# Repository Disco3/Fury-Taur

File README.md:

# Fury-Taur
Fury-Taur is a dualstage J201 Fuzz that mounts internally on a Push-Pull Pot

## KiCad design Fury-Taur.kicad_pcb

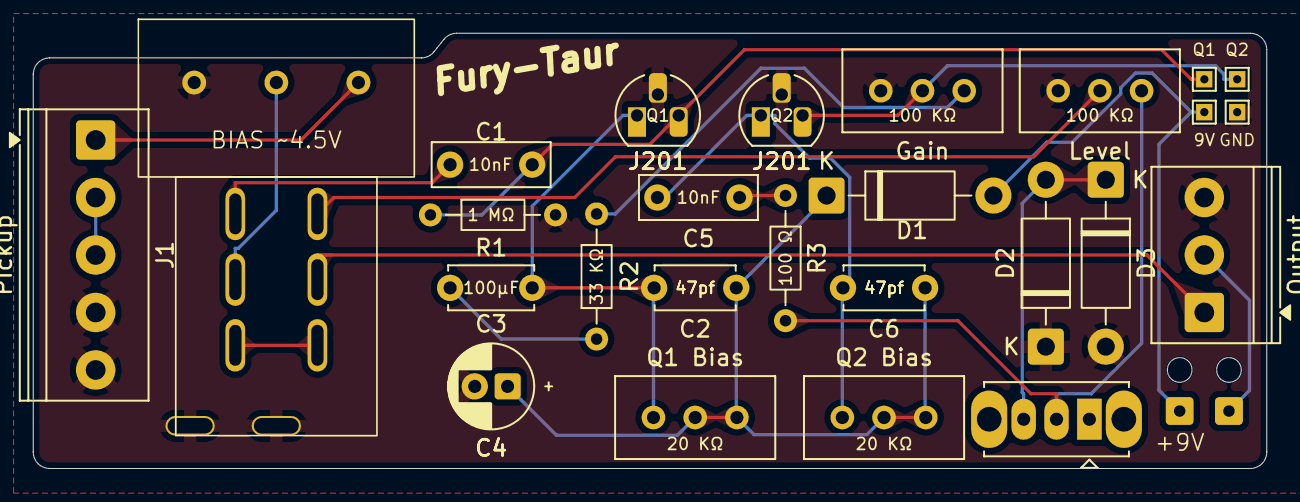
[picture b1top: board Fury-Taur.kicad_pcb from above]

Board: 2 copper layers, 75.1 x 26.5 mm, 30 parts (0 on the bottom side), 20 nets.

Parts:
9V: TestPoint_THTPad_1.0x1.0mm_Drill0.5mm
9V+: SolderWire-0.127sqmm_1x01_D0.48mm_OD1mm
BAT-: SolderWire-0.127sqmm_1x01_D0.48mm_OD1mm
C1, C5: 10nf; C_Disc_D7.0mm_W2.5mm_P5.00mm
C2, C6: 47pf; C_Disc_D4.7mm_W2.5mm_P5.00mm
C3: 4.7nf; C_Disc_D5.0mm_W2.5mm_P5.00mm
C4: 100uf; CP_Radial_D5.0mm_P2.00mm
D1: 1N5817; D_DO-41_SOD81_P10.16mm_Horizontal
D2, D3: 1N34A; D_DO-41_SOD81_P10.16mm_Horizontal
GND: TestPoint_THTPad_1.0x1.0mm_Drill0.5mm
J1: Pickup; TerminalBlock_Phoenix_PT-1,5-5-3.5-H_1x05_P3.50mm_Horizontal
J2: Output; TerminalBlock_Phoenix_PT-1,5-3-3.5-H_1x03_P3.50mm_Horizontal
Q1, Q2: J201; TO-92L_HandSolder
Q1 Test, Q2 Test: TestPoint_THTPad_1.0x1.0mm_Drill0.5mm
R1: 1M; R_Axial_DIN0204_L3.6mm_D1.6mm_P7.62mm_Horizontal
R2: 33K; R_Axial_DIN0204_L3.6mm_D1.6mm_P7.62mm_Horizontal
R3: 100; R_Axial_DIN0204_L3.6mm_D1.6mm_P7.62mm_Horizontal
RV1: PushPull_Pot_DPDT
RV2, RV3: 20K; Potentiometer_Bourns_3296W_Vertical
RV4, RV5: 100K A; Potentiometer_Bourns_3296W_Vertical
SW1: SW_SPDT; SW_Slide_SPDT_Straight_CK_OS102011MS2Q
TH1, TH2: ToolingHole_1.152mm

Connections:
+9V: 9V.1, 9V+.1, D1.2 (A)
BAT -: BAT-.1, J2.2
GND: C4.2, D2.1 (K), D3.2 (A), GND.1, J1.1, J1.2, J2.3, Q1.2 (S), Q2.2 (S), R1.2, RV1.3 (CW), RV1.10 (Case), RV4.3, RV5.3
unnamed: C3.1, R2.1
unnamed: C5.1, R3.1
unnamed: C2.1, C4.1, C6.1, D1.1 (K), RV2.1, RV2.2, RV3.1, RV3.2
unnamed: D2.2 (A), D3.1 (K), SW1.3 (C)
unnamed: J1.3, J1.4
unnamed: J1.5, RV1.1 (CCW)
unnamed: J2.1, RV1.8 (B-Com)
unnamed: C2.2, C3.2, Q1.1 (D), RV2.3
unnamed: C1.1, Q1.3 (G), Q1 Test.1, R1.1
unnamed: C5.2, C6.2, Q2.1 (D), RV3.3
unnamed: Q2.3 (G), Q2 Test.1, RV4.2
unnamed: R2.2, RV4.1
unnamed: RV1.2 (Wiper), RV1.5 (A-Com)
unnamed: C1.2, RV1.4 (A1)
unnamed: RV1.6 (A2), RV1.9 (B2)
unnamed: RV1.7 (B1), RV5.2
unnamed: R3.2, RV5.1, SW1.2 (B)

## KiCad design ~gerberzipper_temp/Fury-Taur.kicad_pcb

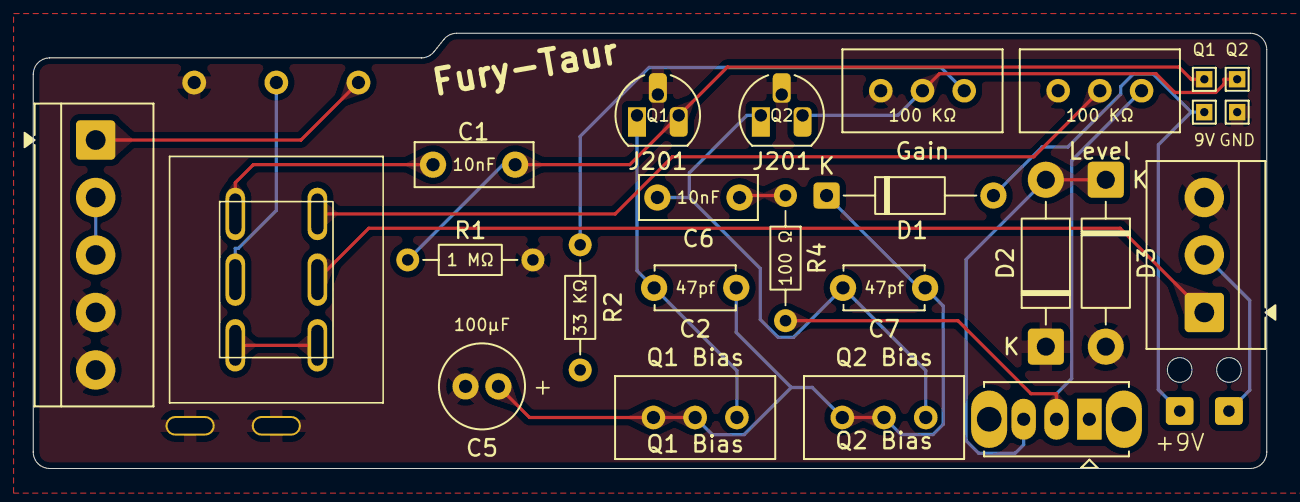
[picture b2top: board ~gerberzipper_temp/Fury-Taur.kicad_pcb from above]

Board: 2 copper layers, 75.1 x 26.5 mm, 31 parts (0 on the bottom side), 19 nets.

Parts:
9V: TestPoint_THTPad_1.0x1.0mm_Drill0.5mm
9V+: SolderWire-0.127sqmm_1x01_D0.48mm_OD1mm
BAT-: SolderWire-0.127sqmm_1x01_D0.48mm_OD1mm
C1, C6: 10nf; C_Disc_D7.0mm_W2.5mm_P5.00mm
C2, C7: 47pf; C_Disc_D4.7mm_W2.5mm_P5.00mm
C5: 100μF; C_Radial_D5.0mm_H11.0mm_P2.00mm
D1: 1N5817; D_DO-35_SOD27_P10.16mm_Horizontal
D2, D3: 1N34A; D_DO-41_SOD81_P10.16mm_Horizontal
GND: TestPoint_THTPad_1.0x1.0mm_Drill0.5mm
J1: Pickup; TerminalBlock_4Ucon_1x05_P3.50mm_Horizontal
J2: Output; TerminalBlock_4Ucon_1x03_P3.50mm_Horizontal
PushPushGround: PushPushGround
Q1, Q2: J201; TO-92L_HandSolder
Q1 Bias, Q2 Bias: 20K; Potentiometer_Bourns_3296W_Vertical
Q1 Test, Q2 Test: TestPoint_THTPad_1.0x1.0mm_Drill0.5mm
R1: 1M; R_Axial_DIN0204_L3.6mm_D1.6mm_P7.62mm_Horizontal
R2: 33K; R_Axial_DIN0204_L3.6mm_D1.6mm_P7.62mm_Horizontal
R3: Gain; Potentiometer_Bourns_3296W_Vertical
R4: 100; R_Axial_DIN0204_L3.6mm_D1.6mm_P7.62mm_Horizontal
R5: Level; Potentiometer_Bourns_3296W_Vertical
RV1J: TO_POT_LUGS; Pot_Lug_Jumper_Pads_Above_SW
SW1: ALPHA_PUSH_PULL; Alpha_PushPull_DirectSwitch_TightSlots
SW2: SW_SPDT; SW_Slide_SPDT_Straight_CK_OS102011MS2Q
TH1, TH2: ToolingHole_1.152mm

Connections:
+9V: 9V.1, 9V+.1, D1.2 (A)
BAT -: BAT-.1, J2.2
COMMON: SW1.6, SW1.9
GND: C5.2, D2.1, D3.2, GND.1, J1.1, J1.2, J2.3, PushPushGround.10, Q1.2 (S), Q2.2 (S), R1.2, R3.3, R5.3, RV1J.1, SW1.10
unnamed: C1.2, SW1.4
unnamed: C6.1, R4.1
unnamed: C2.1, C5.1, C7.1, D1.1 (K), Q1 Bias.2, Q1 Bias.3, Q2 Bias.2, Q2 Bias.3
unnamed: D2.2, D3.1, SW2.3 (C)
unnamed: J1.3, J1.4
unnamed: C2.2, Q1.1 (D), Q1 Bias.1
unnamed: C1.1, Q1.3 (G), Q1 Test.1, R1.1
unnamed: C6.2, C7.2, Q2.1 (D), Q2 Bias.1
unnamed: Q2.3 (G), Q2 Test.1, R3.2
unnamed: R2.2, R3.1
unnamed: R5.2, SW1.7
unnamed: R4.2, R5.1, SW2.2 (B)
PU_NORTH_START: J1.5, RV1J.3
VOL_OUT_TO_JACK_TIP: J2.1, SW1.8
VOL_OUT_TO_SWITCH: RV1J.2, SW1.5
